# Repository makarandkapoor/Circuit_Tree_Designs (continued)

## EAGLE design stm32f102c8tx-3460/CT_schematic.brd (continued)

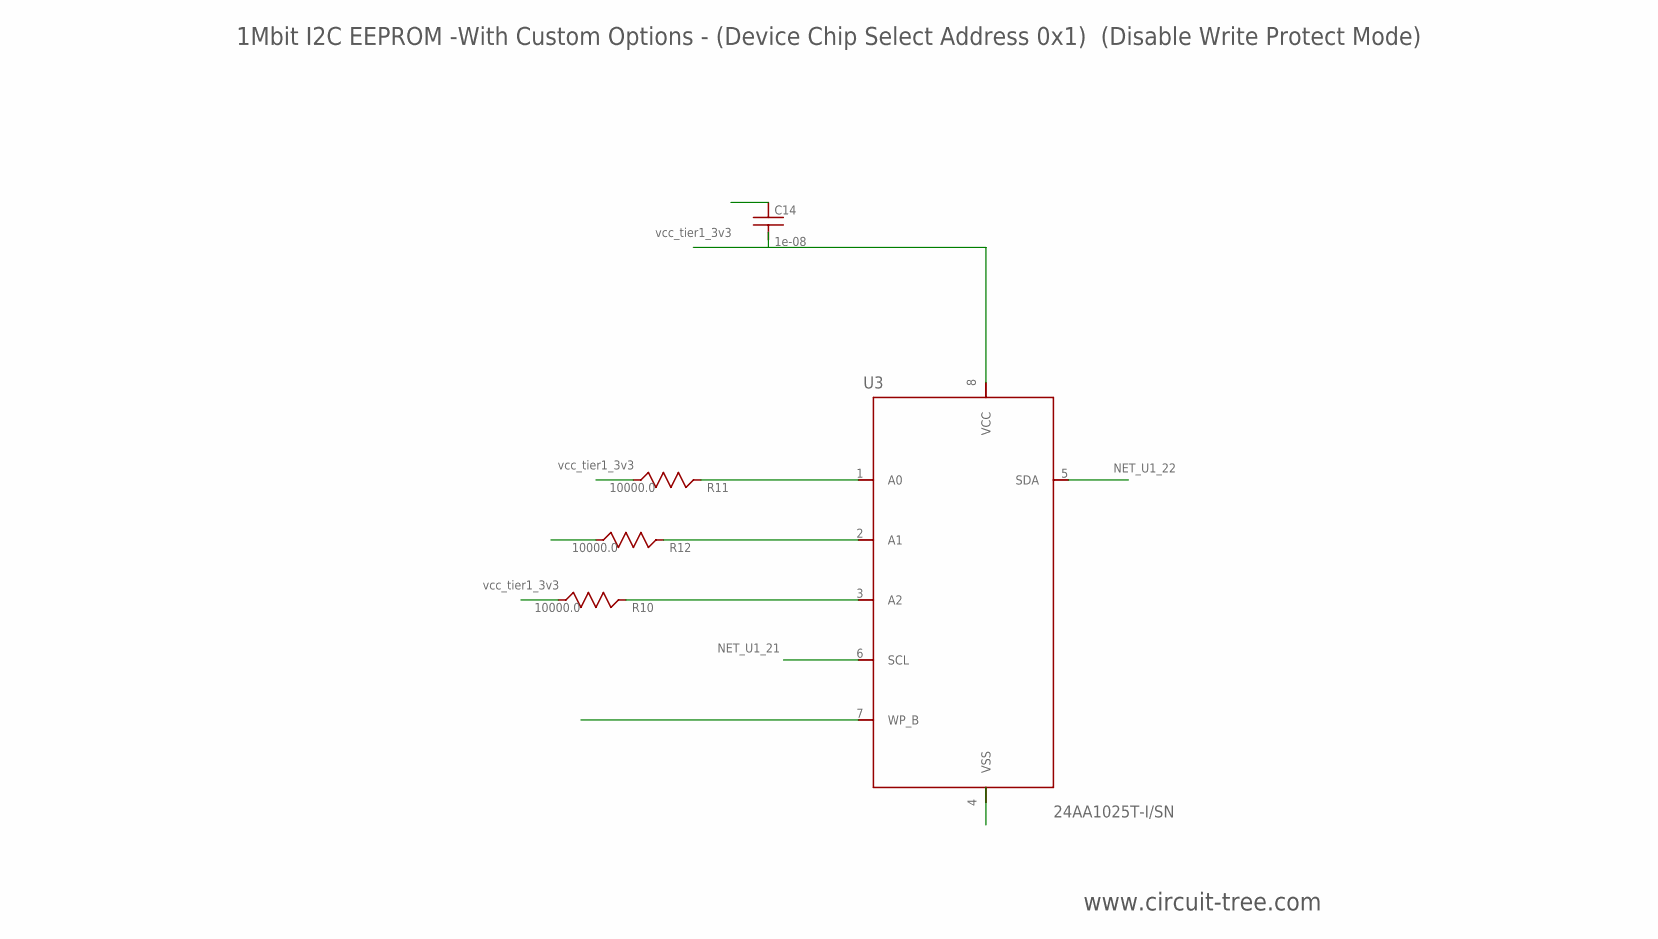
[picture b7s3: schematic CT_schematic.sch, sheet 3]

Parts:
C14: 1e-08; C0402
R10, R11, R12: 10000.0; R0603
U3: 24AA1025T-I/SN; SOIC-8

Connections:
GND: C14.2, R12.2, U3.4 (VSS), U3.7 (WP_B); also elsewhere on the board
NET_U1_21: U3.6 (SCL); also elsewhere on the board
NET_U1_22: U3.5 (SDA); also elsewhere on the board
NET_U3_1: R11.1, U3.1 (A0)
NET_U3_2: R12.1, U3.2 (A1)
NET_U3_3: R10.1, U3.3 (A2)
VCC_TIER1_3V3: C14.1, R10.2, R11.2, U3.8 (VCC); also elsewhere on the board

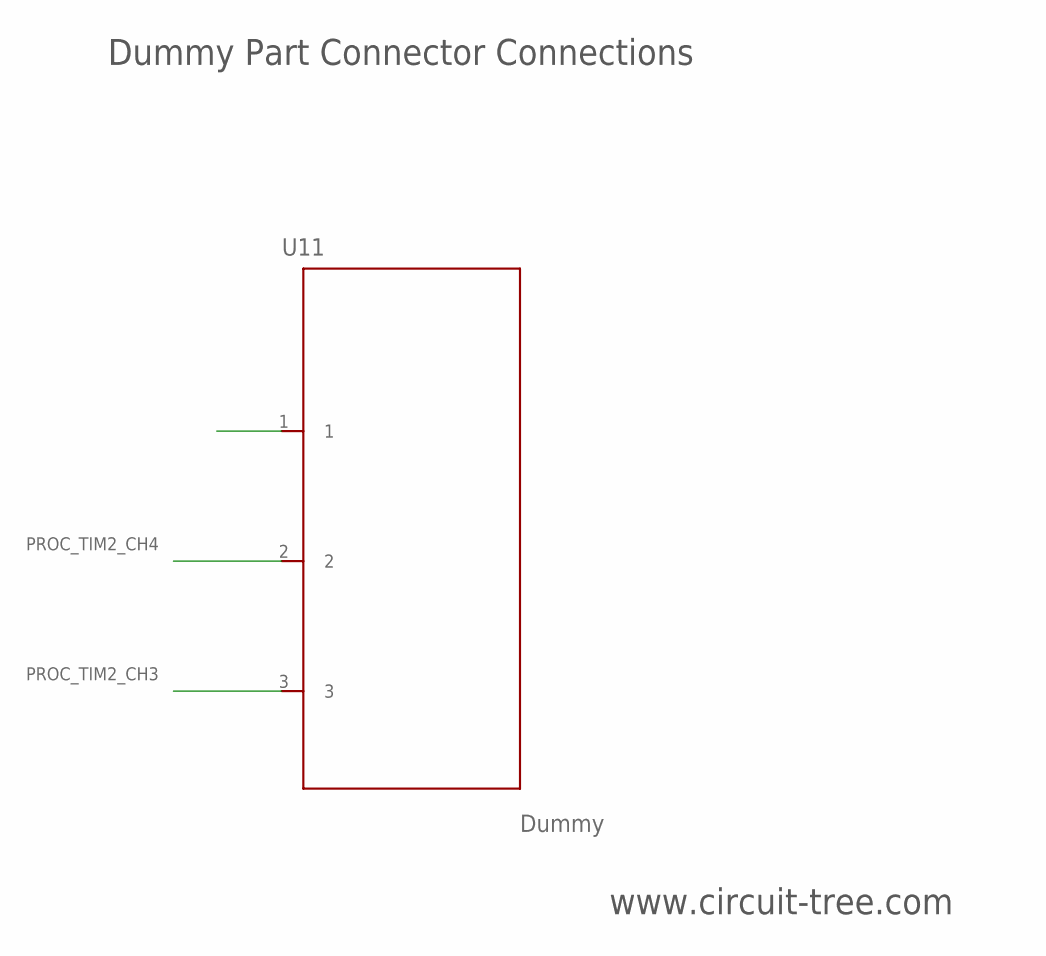
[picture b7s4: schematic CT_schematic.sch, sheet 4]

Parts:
U11: Dummy; DUMMY_PACKAGE_113

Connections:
GND: U11.1; also elsewhere on the board
PROC_TIM2_CH3: U11.3; also elsewhere on the board
PROC_TIM2_CH4: U11.2; also elsewhere on the board

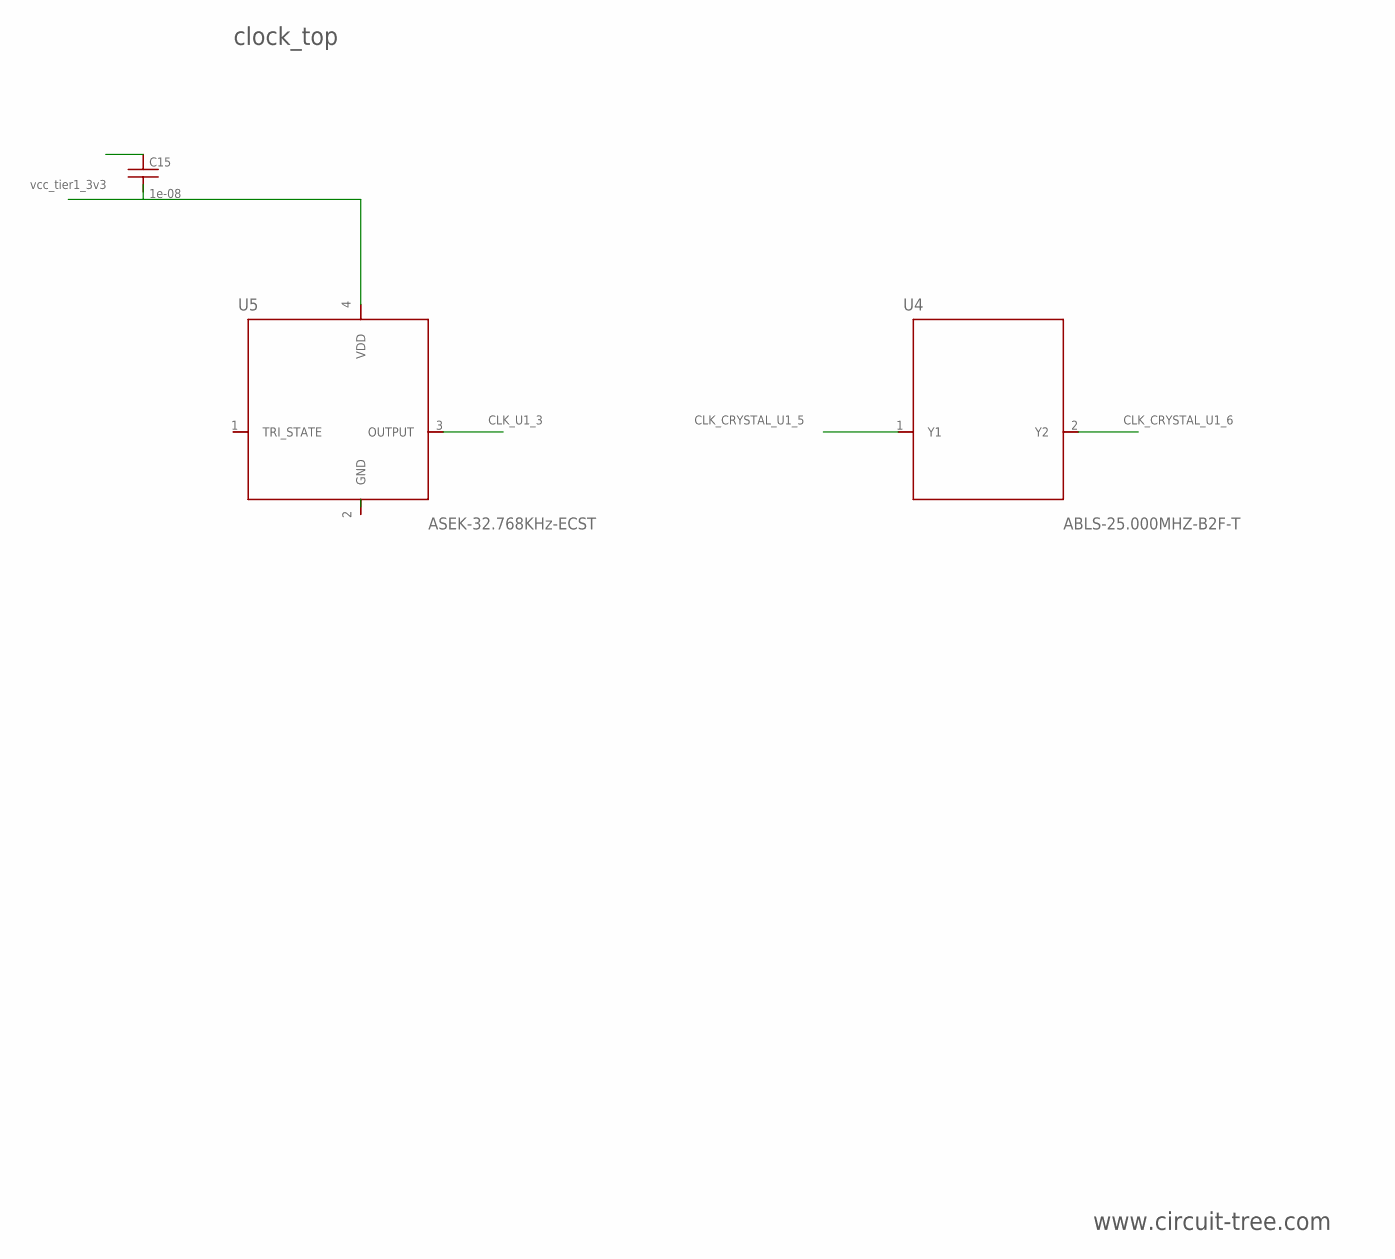
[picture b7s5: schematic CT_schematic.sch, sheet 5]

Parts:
C15: 1e-08; C0402
U4: ABLS-25.000MHZ-B2F-T
U5: ASEK-32.768KHz-ECST; ASEK

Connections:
CLK_CRYSTAL_U1_5: U4.1 (Y1); also elsewhere on the board
CLK_CRYSTAL_U1_6: U4.2 (Y2); also elsewhere on the board
CLK_U1_3: U5.3 (OUTPUT); also elsewhere on the board
GND: C15.2, U5.2 (GND); also elsewhere on the board
VCC_TIER1_3V3: C15.1, U5.4 (VDD); also elsewhere on the board

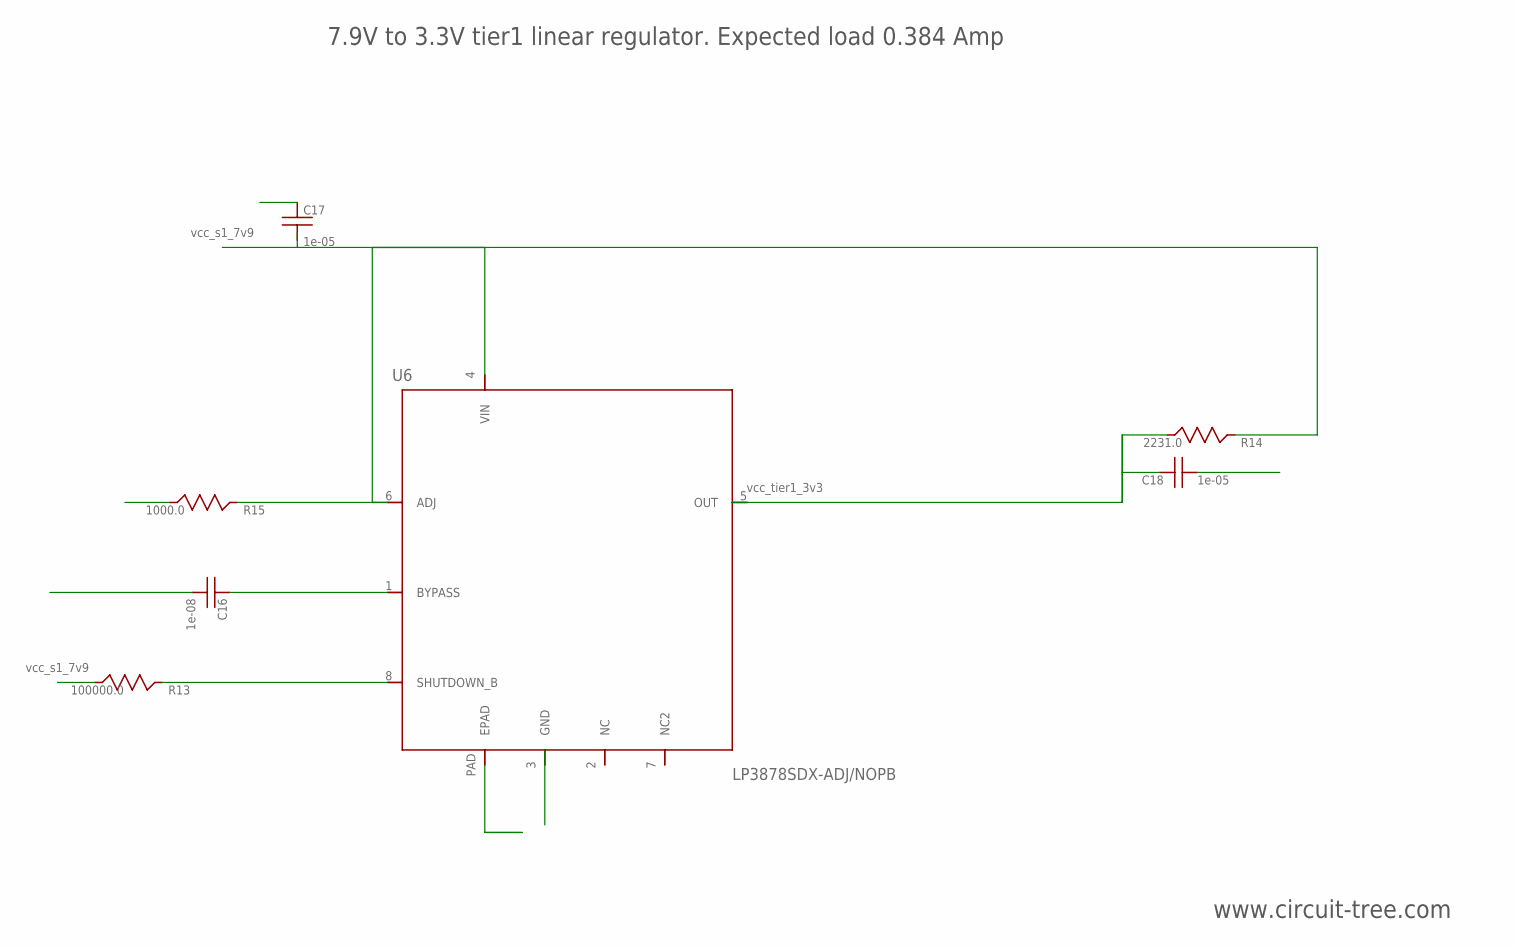
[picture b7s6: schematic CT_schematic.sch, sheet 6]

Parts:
C16: 1e-08; C0402
C17: 1e-05; C1206
C18: 1e-05; C1210
R13: 100000.0; R0603
R14: 2231.0; R0603
R15: 1000.0; R0603
U6: LP3878SDX-ADJ/NOPB; WSON-8

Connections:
GND: C16.2, C17.2, C18.2, R15.2, U6.3 (GND), U6.PAD (EPAD); also elsewhere on the board
NET_U6_1: C16.1, U6.1 (BYPASS)
NET_U6_6: R14.2, R15.1, U6.6 (ADJ)
NET_U6_8: R13.1, U6.8 (SHUTDOWN_B)
VCC_S1_7V9: C17.1, R13.2, U6.4 (VIN); also elsewhere on the board
VCC_TIER1_3V3: C18.1, R14.1, U6.5 (OUT); also elsewhere on the board

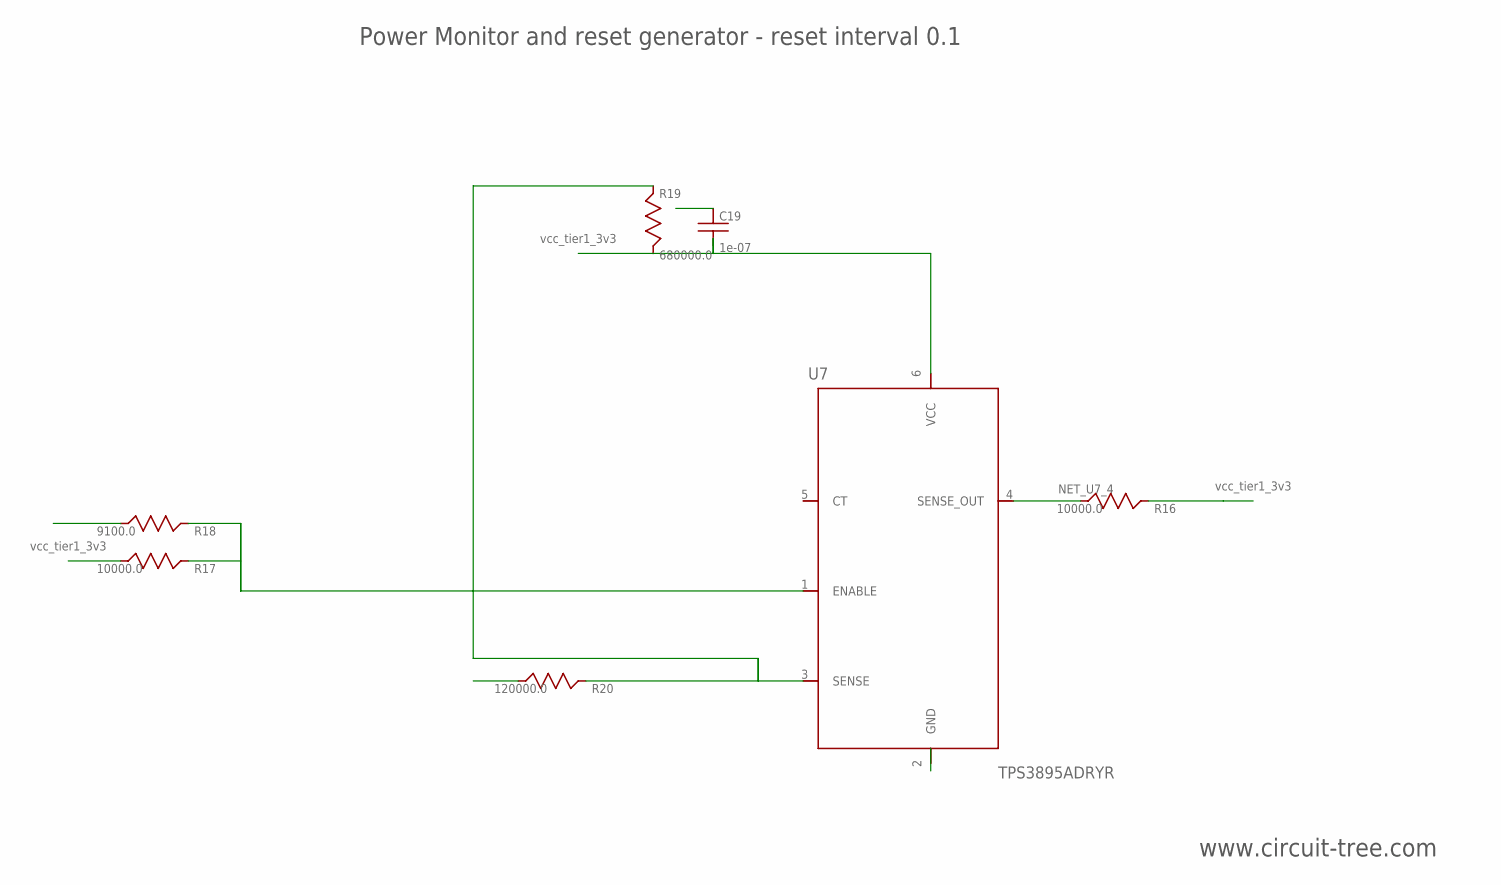
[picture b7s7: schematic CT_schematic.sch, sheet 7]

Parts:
C19: 1e-07; C0402
R16, R17: 10000.0; R0603
R18: 9100.0; R0603
R19: 680000.0; R0603
R20: 120000.0; R0603
U7: TPS3895ADRYR; SON-6

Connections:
GND: C19.2, R18.2, R20.2, U7.2 (GND); also elsewhere on the board
NET_U7_1: R17.1, R18.1, U7.1 (ENABLE)
NET_U7_3: R19.2, R20.1, U7.3 (SENSE)
NET_U7_4: R16.1, U7.4 (SENSE_OUT); also elsewhere on the board
VCC_TIER1_3V3: C19.1, R16.2, R17.2, R19.1, U7.6 (VCC); also elsewhere on the board

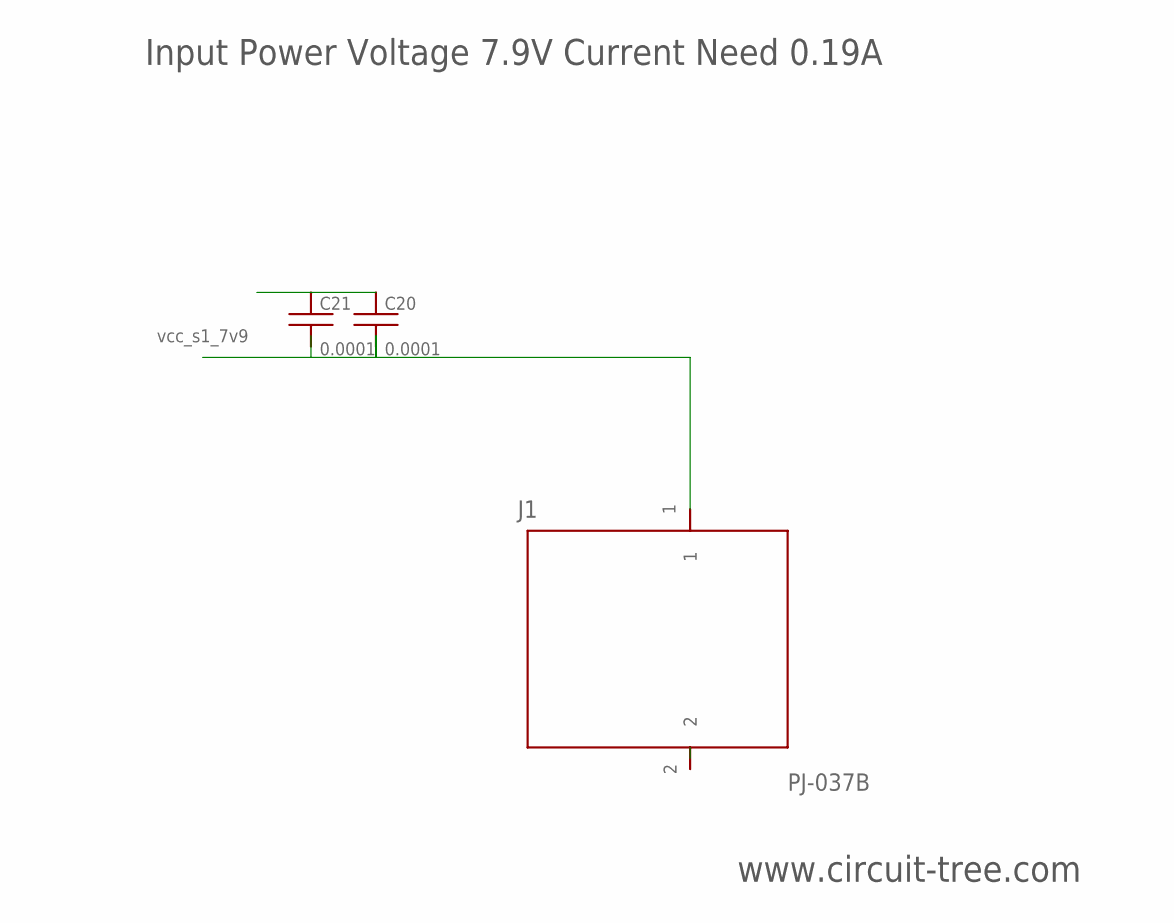
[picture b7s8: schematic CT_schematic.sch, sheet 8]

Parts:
C20, C21: 0.0001; EXV-9H
J1: PJ-037B; PJ-037B_PACKAGE

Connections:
GND: C20.2, C21.2, J1.2; also elsewhere on the board
VCC_S1_7V9: C20.1, C21.1, J1.1; also elsewhere on the board

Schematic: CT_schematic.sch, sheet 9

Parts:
C22: 1e-08; C0402
R2: 1000.0; R0603
U8: 4-1437565-2; SW_4-1437565-2
U9: Q65110A2395; LGM67K-G1J2-24-Z
U10: nc7sz125m5x; NC7SZ125M5X

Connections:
GND: C22.2, R2.2, U9.C, U10.1 (OE1_B), U10.3 (GND); also elsewhere on the board
NET_U1_7: U10.4 (Y); also elsewhere on the board
NET_U1_45: U9.A; also elsewhere on the board
NET_U1_46: U8.3 (POLE2), U8.4 (POLE22); also elsewhere on the board
NET_U7_4: U10.2 (A); also elsewhere on the board
NET_U8_1: R2.1, U8.1 (POLE1), U8.2 (POLE12)
VCC_TIER1_3V3: C22.1, U10.5 (VCC); also elsewhere on the board

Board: 2 copper layers, 55 parts (0 on the bottom side), 27 nets, no tracks yet.

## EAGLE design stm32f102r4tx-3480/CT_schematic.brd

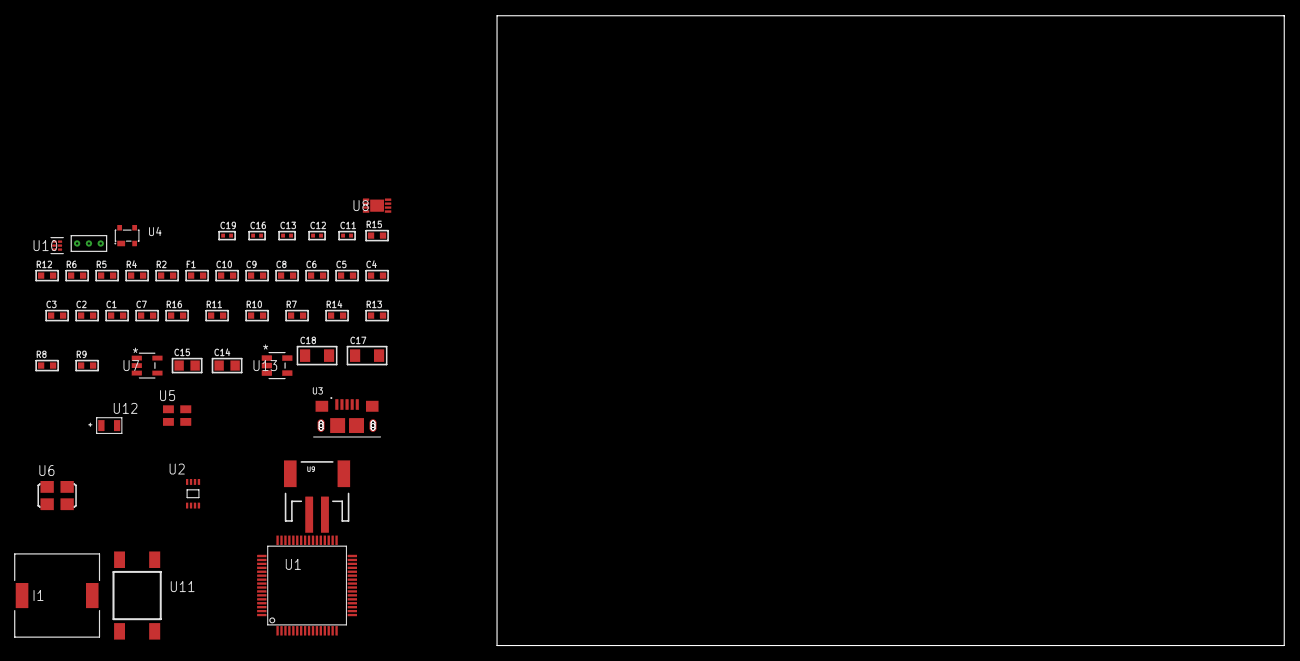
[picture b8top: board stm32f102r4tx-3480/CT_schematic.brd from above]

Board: 2 copper layers, 122.6 x 80.0 mm, 49 parts (0 on the bottom side), 25 nets, no tracks yet.

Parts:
C1, C10: 1e-06; C0603
C2, C3, C4, C5, C6: 1e-07; C0603
C7: 4.7e-06; C0603
C8, C9: 1e-08; C0603
C11, C12, C13, C19: 1e-08; C0402
C14, C15: 1e-05; C0805
C16: 1e-07; C0402
C17, C18: 1e-05; C1206
F1: 240.0; L0603
I1: 2.5e-06; DR1040
R2: 1000.0; R0603
R4: 4700.0; R0603
R5, R6: 2200.0; R0603
R7, R10, R11, R16: 10000.0; R0603
R8: 220000.0; R0603
R9: 1000000.0; R0603
R12: 9100.0; R0603
R13: 680000.0; R0603
R14: 120000.0; R0603
R15: 2000.0; R0603
U1: STM32F102R4T6; LQFP64
U2: 24AA08T-I/MNY; TDFN-8/6MM
U3: 10118193-0001LF; FCI_10118193-0001LF
U4: prtr5v0u2ax; SOT143B
U5: ASEK-32.768KHz-ECST; ASEK
U6: ASFL1-25MHZ-NCS; ASFL1
U7: ltc3406es5; TSOT-23-5
U8: MCP73831T-2ACI/MC; DFN8_2X3MC
U9: S2B-PH-SM4-TB(LF)(SN); JST-2-SMD
U10: TPS3895ADRYR; SON-6
U11: 4-1437565-2; SW_4-1437565-2
U12: Q65110A2395; LGM67K-G1J2-24-Z
U13: nc7sz125m5x; NC7SZ125M5X
U14: Dummy; DUMMY_PACKAGE_107

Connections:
CLK_U1_3: U1.3, U5.3
CLK_U1_5: U1.5, U6.3
GND: C1.2, C2.2, C3.2, C4.2, C5.2, C6.2, C7.2, C8.2, C9.2, C10.2, C11.2, C12.2, C13.2, C14.2, C15.1, C15.2, C16.2, C17.2, C18.2, C19.2, R2.2, R7.2, R8.2, R12.2, R14.2, R15.2, U1.12, U1.18, U1.31, U1.47, U1.63, U2.4, U2.7, U3.5, U3.6, U3.7, U3.8, U3.9, U4.1, U5.2, U6.2, U7.2, U8.6, U8.9, U9.2, U10.2, U12.C, U13.1, U13.3, U14.1
INPUT_USBPOWER_5V: C17.1, R16.2, U3.1, U4.4, U8.1, U8.2
NET_U1_7: R4.1, U1.7, U13.4
NET_U1_13: C8.1, C9.1, C10.1, F1.1, U1.13
NET_U1_58: R5.1, U1.58, U2.6
NET_U1_59: R6.1, U1.59, U2.5
NET_U1_60: R7.1, U1.60
NET_U1_62: U11.3, U11.4
NET_U7_3: I1.1, U7.3
NET_U7_5: R8.1, R9.1, U7.5
NET_U7_ATNET_3: I1.2, R9.2
NET_U8_5: R16.1, U8.5
NET_U8_8: R15.1, U8.8
NET_U10_1: R11.1, R12.1, U10.1
NET_U10_3: R13.2, R14.1, U10.3
NET_U10_4: R10.1, U10.4, U13.2
NET_U11_1: R2.1, U11.1, U11.2
PROC_ADC1_IN3: U1.17, U14.3
PROC_ADC1_IN4: U1.20, U14.2
PROC_USB_DM: U1.44, U3.2, U4.3
PROC_USB_DP: U1.45, U3.3, U4.2
VCC_S1_3V7: C14.1, C18.1, U7.4, U8.3, U8.4, U9.1
VCC_TIER1_3V3: C1.1, C2.1, C3.1, C4.1, C5.1, C6.1, C7.1, C11.1, C12.1, C13.1, C15.2, C16.1, C19.1, F1.2, I1.2, R4.2, R5.2, R6.2, R9.2, R10.2, R11.2, R13.1, U1.1, U1.19, U1.32, U1.48, U1.64, U2.8, U5.4, U6.4, U10.6, U13.5
